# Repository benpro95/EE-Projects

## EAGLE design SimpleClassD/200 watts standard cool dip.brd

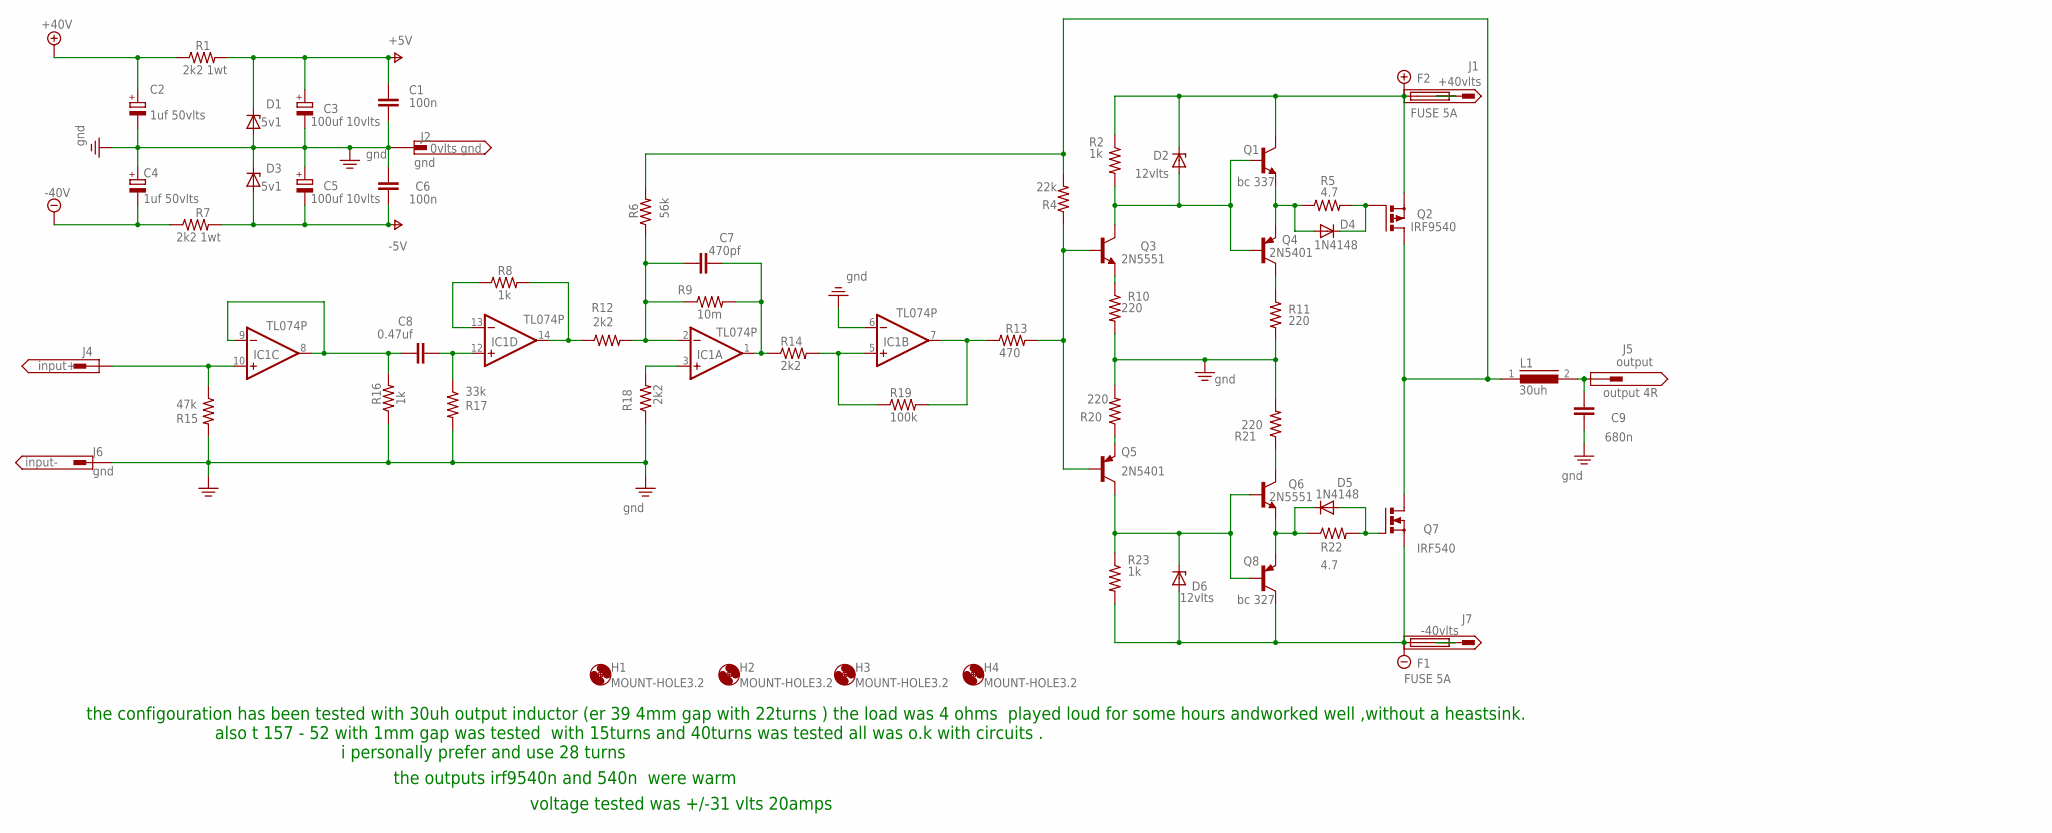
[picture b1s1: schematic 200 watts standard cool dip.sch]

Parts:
C1, C6: 100n; C7.5B5
C2, C4: 1uf 50vlts; E2,5-6
C3, C5: 100uf 10vlts; E3,5-8
C7: 470pf; C5B3.5
C8: 0.47uf; C7.5B6
C9: 680n; C15B6
D1, D3: 5v1; DO34Z7
D2, D6: 12vlts; DO34Z7
D4, D5: 1N4148; DO35-7
F1, F2: FUSE 5A; SHK20L
H1, H2, H3, H4: MOUNT-HOLE3.2; 3,2
IC1: TL074P; DIL14
J1: +40v; F061.040
J2, J6: gnd; F061.040
J4: input; F061.040
J5: output; F061.040
J7: -40v; F061.040
L1: 30uh; SUKW1-17
Q1: bc 337; TO92-CBE
Q2: IRF9540; TO220BV
Q3, Q6: 2N5551; TO92-EBC
Q4, Q5: 2N5401; TO92-EBC
Q7: IRF540; TO220BV
Q8: bc 327; TO92-CBE
R1, R7: 2k2 1wt; 0309/12
R2, R16, R23: 1k; 0207/7
R4: 22k; 0207/7
R5, R22: 4.7; 0207/7
R6: 56k; 0207/7
R8: 1k; 0207/2V
R9: 10m; 0207/2V
R10, R11, R20, R21: 220; 0207/7
R12, R18: 2k2; 0207/7
R13: 470; 0207/7
R14: 2k2; 0207/10
R15: 47k; 0207/2V
R17: 33k; 0207/2V
R19: 100k; 0207/5V

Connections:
+5V: C1.1, C3.+, D1.C, IC1.4 (V+), R1.2
+40V: C2.+, D2.C, F2.1A (1), Q1.C, Q2.S, R1.1, R2.1
-5V: C5.-, C6.2, D3.A, IC1.11 (V-), R7.2
-40V: C4.-, D6.A, F1.1A (1), Q7.S, Q8.C, R7.1, R23.2
GND: C1.2, C2.-, C3.-, C4.+, C5.+, C6.1, C9.1, D1.A, D3.C, IC1.6 (-IN), J2.A1, J2.A2, J6.A1, J6.A2, R10.2, R11.2, R15.2, R16.1, R17.2, R18.1, R20.2, R21.2
unnamed: D5.A, Q7.G, R22.2
unnamed: D4.A, Q1.E, Q4.E, R5.1
unnamed: D4.C, Q2.G, R5.2
unnamed: C9.2, J5.A1, J5.A2, L1.2
unnamed: L1.1, Q2.D, Q7.D, R4.2, R6.2
unnamed: D6.C, Q5.C, Q6.B, Q8.B, R23.1
unnamed: Q6.C, R21.1
unnamed: D5.C, Q6.E, Q8.E, R22.1
unnamed: Q4.C, R11.1
unnamed: Q5.E, R20.1
unnamed: F1.2A (2), J7.A1, J7.A2
unnamed: Q3.E, R10.1
unnamed: D2.A, Q1.B, Q3.C, Q4.B, R2.2
unnamed: F2.2A (2), J1.A1, J1.A2
unnamed: Q3.B, Q5.B, R4.1, R13.2
unnamed: IC1.7 (OUT), R13.1, R19.2
unnamed: IC1.5 (+IN), R14.2, R19.1
unnamed: C7.1, IC1.2 (-IN), R6.1, R9.1, R12.2
unnamed: IC1.3 (+IN), R18.2
unnamed: IC1.14 (OUT), R8.2, R12.1
unnamed: IC1.13 (-IN), R8.1
unnamed: C8.1, IC1.8 (OUT), IC1.9 (-IN), R16.2
unnamed: C7.2, IC1.1 (OUT), R9.2, R14.1
unnamed: C8.2, IC1.12 (+IN), R17.1
unnamed: IC1.10 (+IN), J4.A1, J4.A2, R15.1

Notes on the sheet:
the configouration has been tested with 30uh output inductor (er 39 4mm gap with 22turns ) the load was 4 ohms played loud for some hours andworked well ,without a heastsink.
also t 157 - 52 with 1mm gap was tested with 15turns and 40turns was tested all was o.k with circuits . i personally prefer and use 28 turns
voltage tested was +/-31 vlts 20amps
the outputs irf9540n and 540n were warm

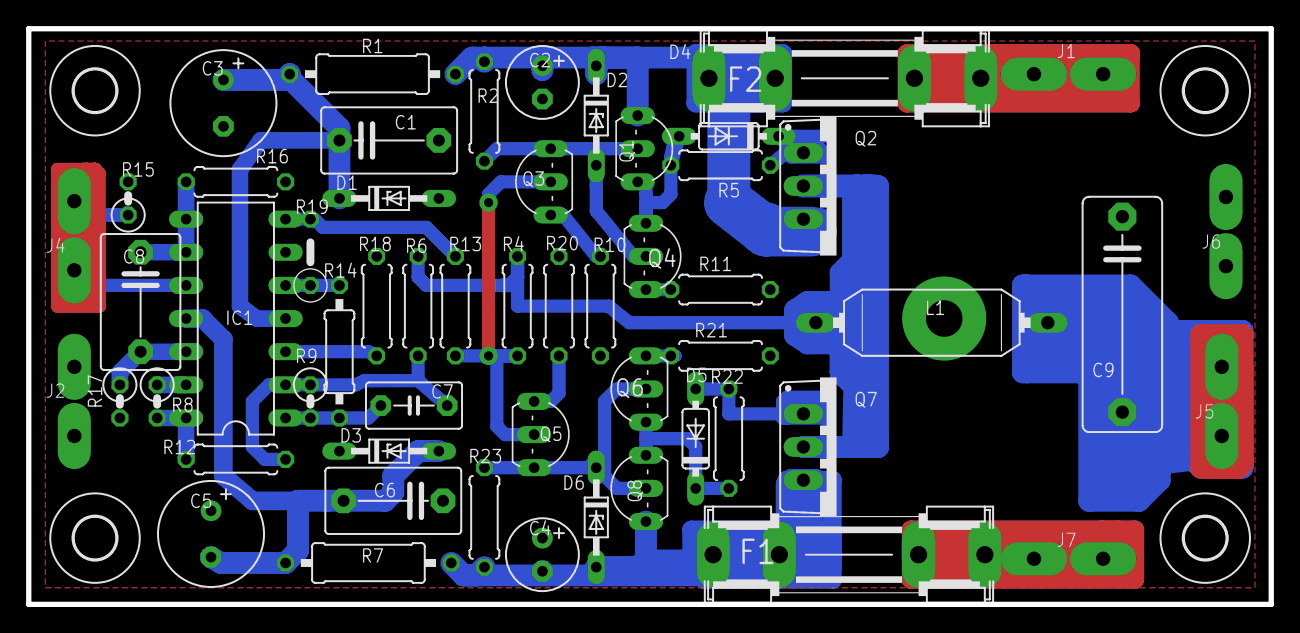
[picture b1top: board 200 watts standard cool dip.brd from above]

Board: 2 copper layers, 95.2 x 44.1 mm, 59 parts (0 on the bottom side), 30 nets.

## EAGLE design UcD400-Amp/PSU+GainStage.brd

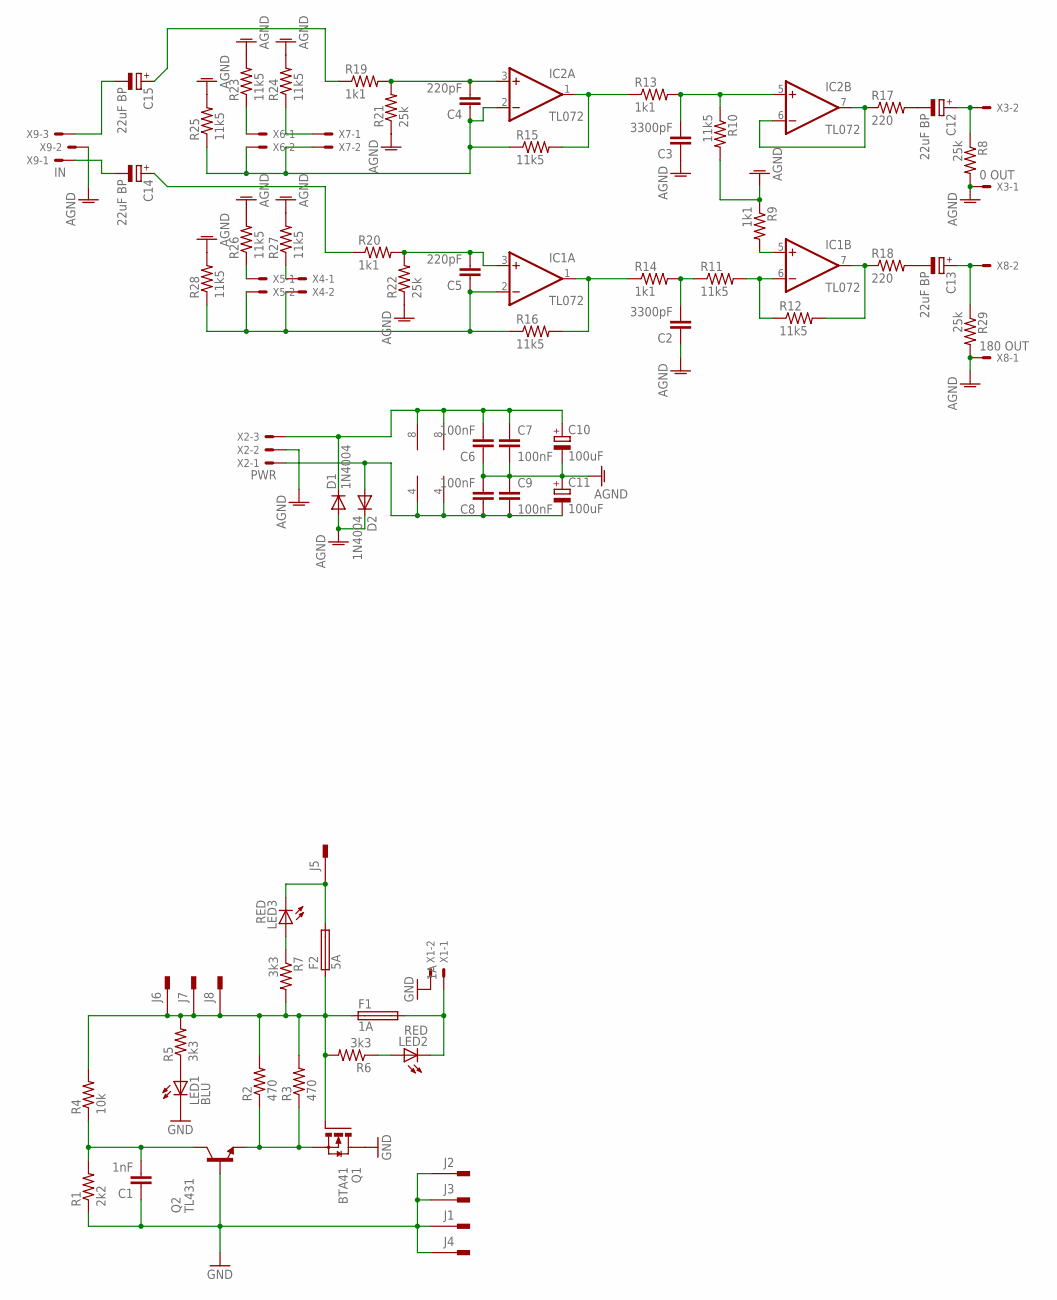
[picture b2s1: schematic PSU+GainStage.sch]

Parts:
C1: 1nF; C050-035X075
C2, C3: 3300pF; C050-035X075
C4, C5: 220pF; C050-035X075
C6, C7, C8, C9: 100nF; C1210
C10, C11: 100uF; E5-8,5
C12, C13, C14, C15: 22uF BP; E3,5-10
D1, D2: 1N4004; DO41-10
F1: 1A; TR5
F2: 5A; TR5
IC1, IC2: TL072; DIL08
J1, J2, J3, J4, J5, J6, J7, J8: PIN2F061.040; F061.040
LED1: BLU; LED5MM
LED2, LED3: RED; LED5MM
Q1: BTA41; TO247BV
Q2: TL431; TO92-EBC
R1: 2k2; 0309/12
R2, R3: 470; 0411/15
R4: 10k; 0309/12
R5, R6, R7: 3k3; 0309/12
R8, R29: 25k; 0309/12
R9, R13, R14, R19: 1k1; 0309/12
R10: 11k5; 0309/12
R11, R12, R15, R16, R23, R24, R25, R26, R27, R28: 11k5; 0309/10
R17: 220; 0309/12
R18: 220; 0309/10
R20: 1k1; 0309/10
R21, R22: 25k; 0309/10
X1: 1A; 22-23-2021
X2: PWR; 22-23-2031
X3: 0 OUT; 22-23-2021
X4, X5, X6, X7: 22-23-2021
X8: 180 OUT; 22-23-2021
X9: IN; 22-23-2031

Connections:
AGND: C2.1, C3.1, C6.1, C7.2, C8.2, C9.1, C10.-, C11.+, D1.A, D2.C, R8.2, R9.1, R10.2, R21.1, R22.1, R23.2, R24.2, R25.2, R26.2, R27.2, R28.2, R29.2, X2.2, X3.1, X8.1, X9.2
GND: C1.1, J1.A1, J1.A2, J2.A1, J2.A2, J3.A1, J3.A2, J4.A1, J4.A2, LED1.K (C), Q1.D, Q2.B, R1.1, X1.2
unnamed: Q1.S, Q2.E, R2.1, R3.1
unnamed: F1.1, F2.1, J6.A1, J6.A2, J7.A1, J7.A2, J8.A1, J8.A2, Q1.G, R2.2, R3.2, R4.2, R5.2, R6.2, R7.2
unnamed: C1.2, Q2.C, R1.2, R4.1
unnamed: LED3.A, R7.1
unnamed: F2.2, J5.A1, J5.A2, LED3.K (C)
unnamed: LED1.A, R5.1
unnamed: F1.2, LED2.K (C), X1.1
unnamed: LED2.A, R6.1
unnamed: C12.-, R17.2
unnamed: C6.2, C7.1, C10.+, D1.C, IC1.8 (V+), IC2.8 (V+), X2.3
unnamed: C8.1, C9.2, C11.-, D2.A, IC1.4 (V-), IC2.4 (V-), X2.1
unnamed: IC2.6 (-IN), IC2.7 (OUT), R17.1
unnamed: IC1.5 (+IN), R9.2
unnamed: C3.2, IC2.5 (+IN), R10.1, R13.2
unnamed: IC1.6 (-IN), R11.2, R12.1
unnamed: IC1.7 (OUT), R12.2, R18.1
unnamed: C2.2, R11.1, R14.2
unnamed: IC2.1 (OUT), R13.1, R15.2
unnamed: IC1.1 (OUT), R14.1, R16.2
unnamed: C4.2, IC2.3 (+IN), R19.2, R21.2
unnamed: C4.1, IC2.2 (-IN), R15.1, R25.1, X6.2, X7.2
unnamed: C5.1, IC1.2 (-IN), R16.1, R28.1, X4.2, X5.2
unnamed: C5.2, IC1.3 (+IN), R20.2, R22.2
unnamed: R26.1, X5.1
unnamed: R27.1, X4.1
unnamed: R24.1, X7.1
unnamed: R23.1, X6.1
unnamed: C13.-, R18.2
unnamed: C12.+, R8.1, X3.2
unnamed: C13.+, R29.1, X8.2
unnamed: C15.+, R19.1
unnamed: C14.+, R20.1
unnamed: C14.-, X9.1
unnamed: C15.-, X9.3

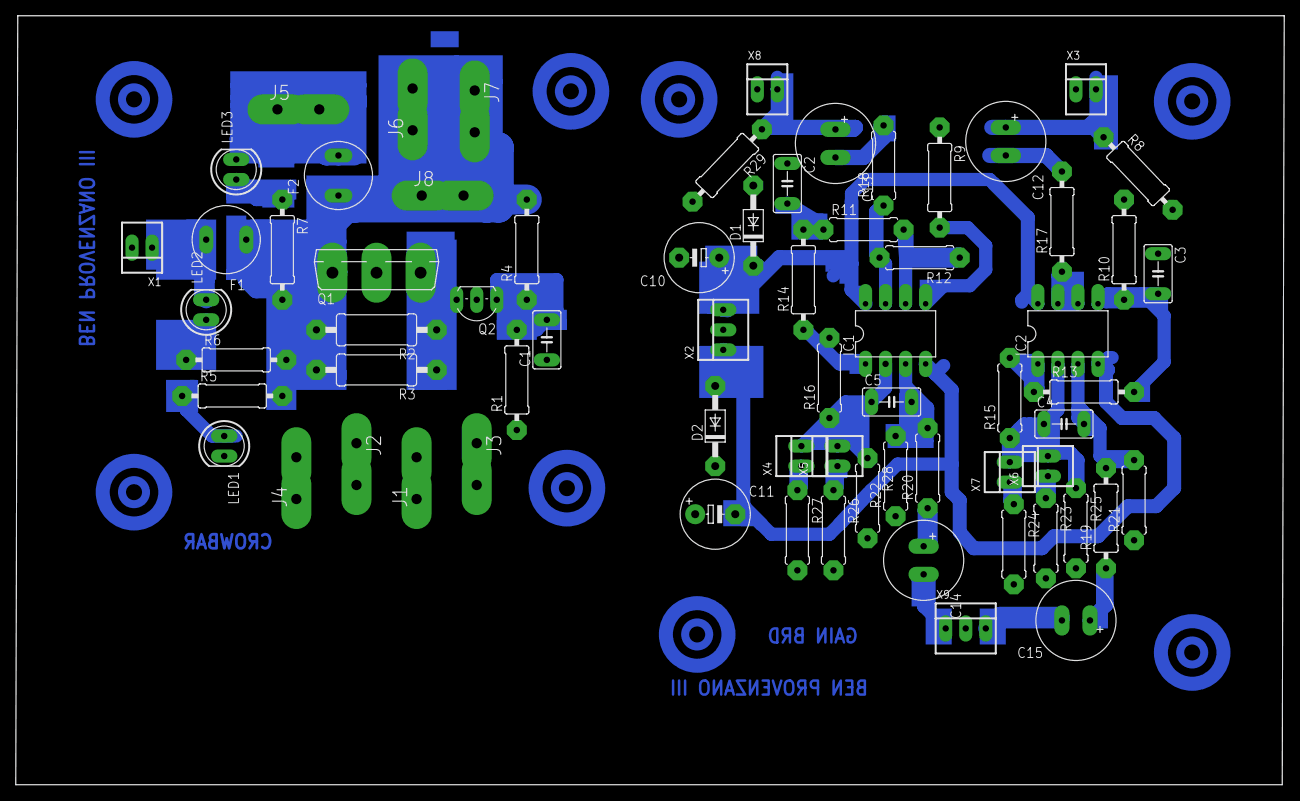
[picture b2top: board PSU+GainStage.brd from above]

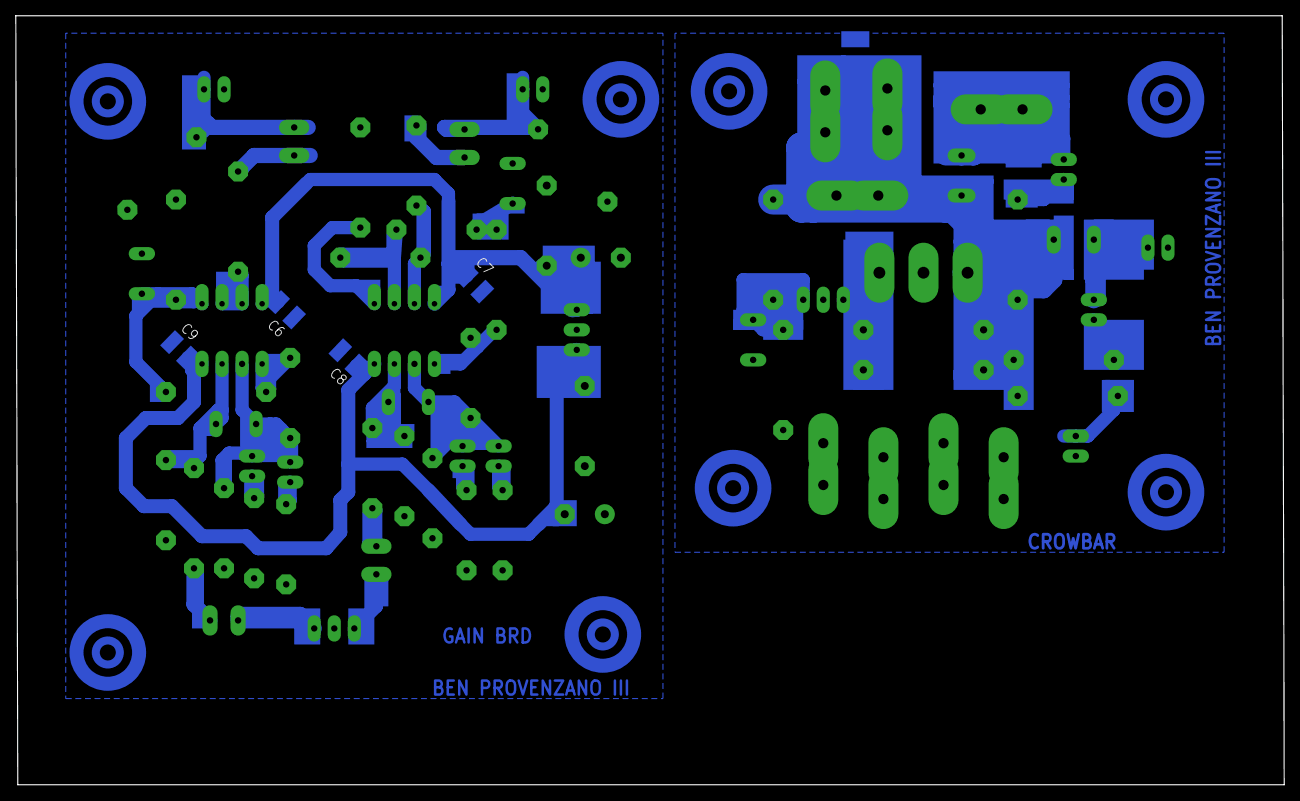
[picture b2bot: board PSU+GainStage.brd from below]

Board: 2 copper layers, 160.8 x 97.5 mm, 72 parts (4 on the bottom side), 36 nets.

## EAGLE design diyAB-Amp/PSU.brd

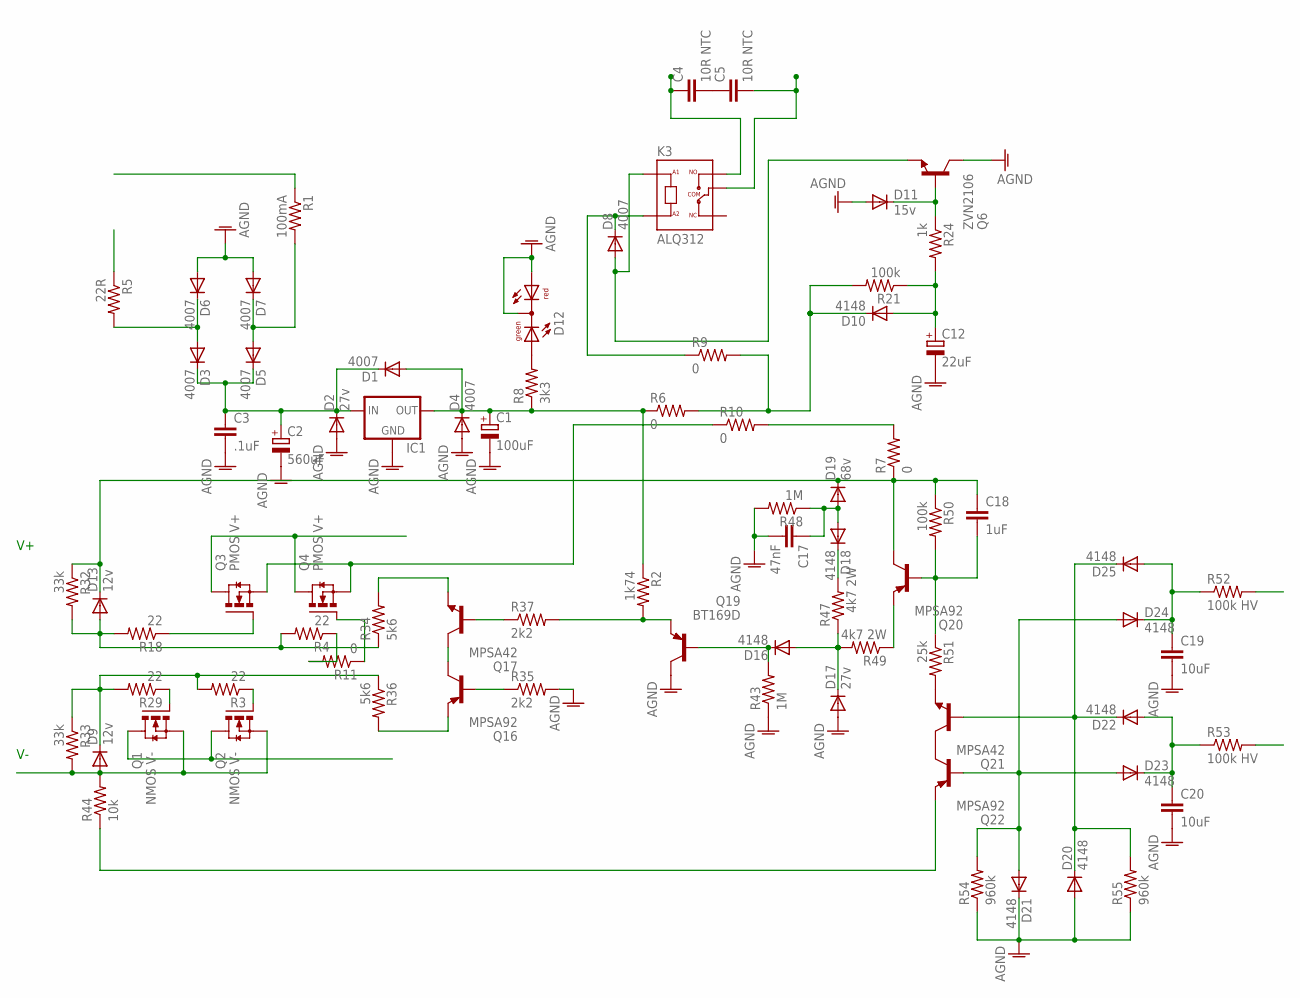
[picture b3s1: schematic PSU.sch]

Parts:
C1: 100uF; E3,5-10
C2: 560uF; E5-13
C3: .1uF; C075-032X103
C4, C5: 10R NTC; C075-063X106
C12: 22uF; E2,5-7
C17: 47nF; C050-035X075
C18: 1uF; C050-035X075
C19, C20: 10uF; C050-075X075
D1, D3, D4, D5, D6, D7, D8: 4007; DO41-10
D2, D17: 27v; DO41-10
D9, D13: 12v; DO41-10
D10: 4148; DO35-10
D11: 15v; DO35-7
D12: DUOLED5MM
D16, D18: 4148; DO41-10
D19: 68v; DO41-10
D20, D21, D22, D23, D24, D25: 4148; DO35-7
IC1: 78XXS
K3: ALQ312; RELAY_ALQ112
Q1, Q2: NMOS V-; TO247BV
Q3, Q4: PMOS V+; TO247BV
Q6: ZVN2106; TO92-EBC
Q16, Q20, Q22: MPSA92; TO92-EBC
Q17, Q21: MPSA42; TO92-EBC
Q19: BT169D; TO92-EBC
R1: 100mA; 0207/5V
R2: 1k74; 0309/10
R3, R4: 22; 0309/12
R5: 22R; 0309/12
R6, R7, R10, R11: 0; 0309/12
R8: 3k3; 0309/10
R9: 0; 0309/10
R18, R29: 22; 0207/15
R21, R50: 100k; 0309/10
R24: 1k; 0309/10
R32, R33: 33k; 0411/15
R34, R36: 5k6; 0411/15
R35, R37: 2k2; 0309/10
R43: 1M; 0309/10
R44: 10k; 0411/15
R47, R49: 4k7 2W; 0309/10
R48: 1M; 0411/15
R51: 25k; 0309/10
R52, R53: 100k HV; 0309/12
R54, R55: 960k; 0309/10

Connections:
AGND: C1.-, C2.-, C3.2, C12.-, C17.2, C19.2, C20.2, D2.A, D4.A, D6.A, D7.A, D11.A, D12.AR, D12.K (C), D17.A, D20.A, D21.C, IC1.GND, Q6.C, Q19.C, R35.2, R43.1, R48.2, R54.1, R55.1
unnamed: C2.+, C3.1, D1.C, D2.C, D3.C, D5.C, IC1.IN
unnamed: D3.A, D6.C, R5.2
unnamed: C1.+, D1.A, D4.C, IC1.OUT, R2.1, R6.1, R8.1
unnamed: D5.A, D7.C, R1.2
unnamed: C4.1, K3.5 (NO)
unnamed: Q3.G, R18.1
unnamed: Q1.G, R29.1
unnamed: R4.1, R11.2
unnamed: Q2.G, R3.1
unnamed: D8.A, K3.1 (A1), Q6.E
unnamed: D10.C, R6.2, R9.2, R21.2
unnamed: C5.2, K3.3 (COM)
unnamed: D8.C, K3.2 (A2), R9.1
unnamed: R7.2, R10.2
unnamed: D12.AG, R8.2
unnamed: D9.C, R3.2, R29.2, R33.1, R36.1
unnamed: Q4.G, R11.1
unnamed: Q3.S, Q4.S, R10.1
unnamed: C4.2, C5.1
unnamed: C12.+, D10.A, R21.1, R24.2
unnamed: D11.C, Q6.B, R24.1
unnamed: Q3.D, Q4.D
unnamed: D9.A, Q1.S, Q2.S, R33.2, R44.2
unnamed: Q1.D, Q2.D
unnamed: D13.A, R4.2, R18.2, R32.2, R34.1
unnamed: Q17.E, R34.2
unnamed: Q16.E, R36.2
unnamed: Q16.C, Q17.C
unnamed: Q16.B, R35.1
unnamed: Q17.B, R37.1
unnamed: Q19.E, R2.2, R37.2
unnamed: D16.C, Q19.B, R43.2
unnamed: C18.1, D13.C, D19.C, Q20.C, R7.1, R32.1, R50.1
unnamed: Q22.E, R44.1
unnamed: Q20.E, R49.1
unnamed: D16.A, D17.C, R47.1, R49.2
unnamed: D18.C, R47.2
unnamed: C17.1, D18.A, D19.A, R48.1
unnamed: C18.2, Q20.B, R50.2, R51.1
unnamed: Q21.E, R51.2
unnamed: Q21.C, Q22.C
unnamed: D21.A, D23.A, D24.A, Q22.B, R54.2
unnamed: D20.C, D22.C, D25.C, Q21.B, R55.2
unnamed: C20.1, D22.A, D23.C, R53.1
unnamed: C19.1, D24.C, D25.A, R52.1

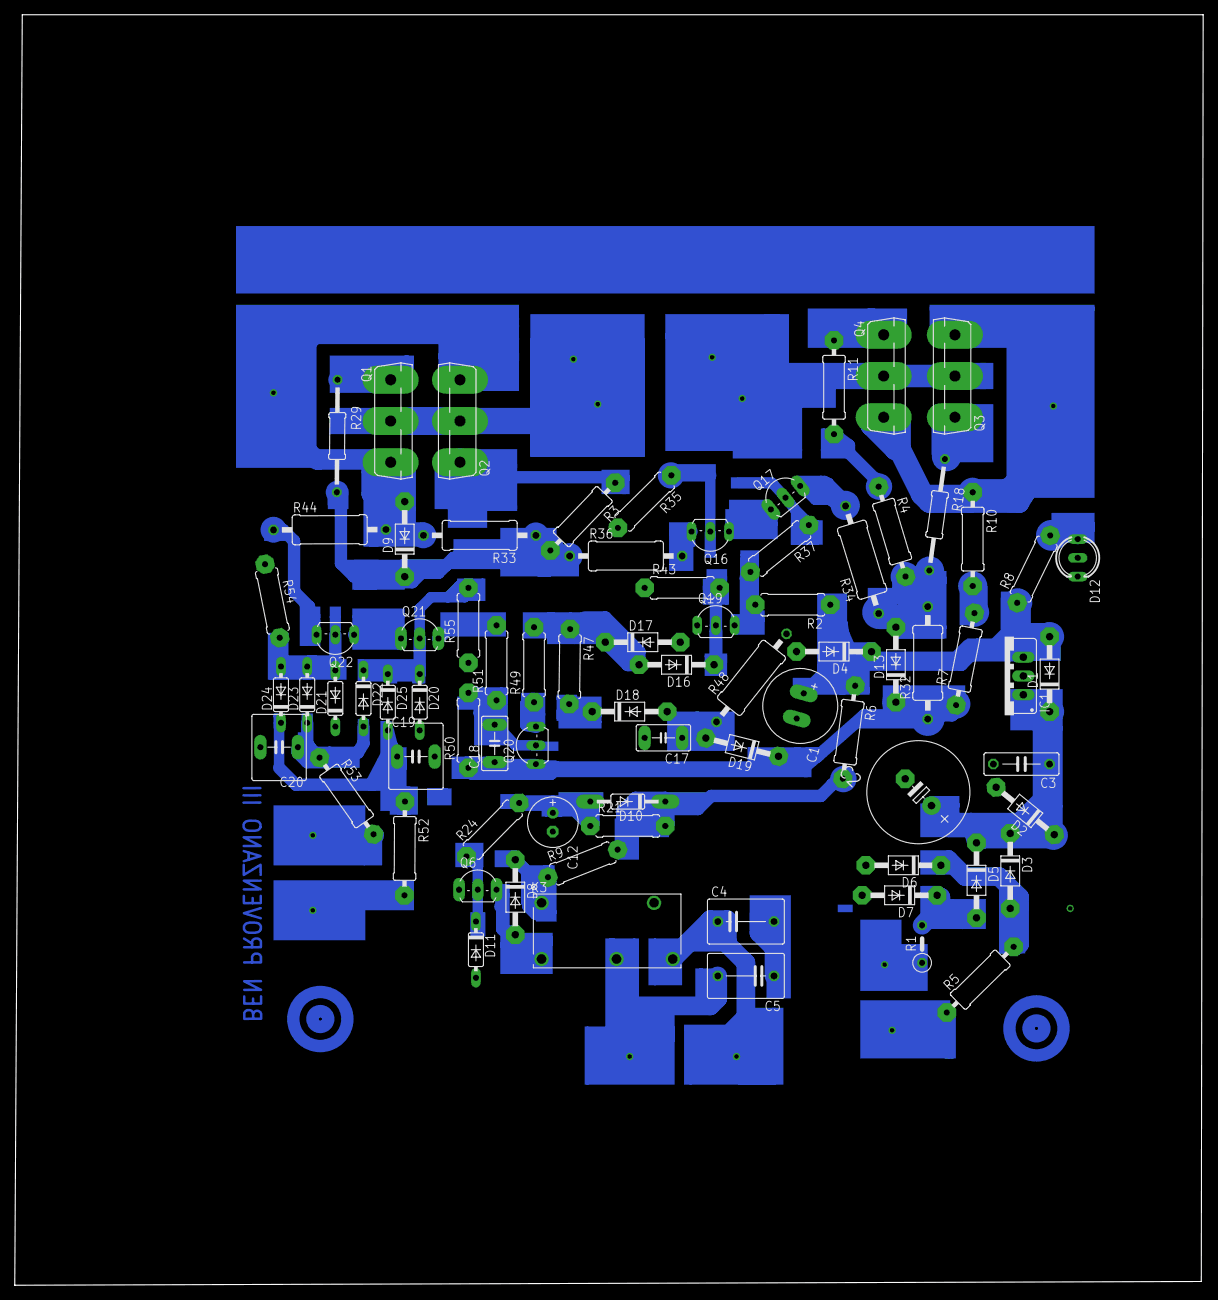
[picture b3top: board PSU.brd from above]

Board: 2 copper layers, 161.0 x 172.1 mm, 78 parts (0 on the bottom side), 46 nets.
